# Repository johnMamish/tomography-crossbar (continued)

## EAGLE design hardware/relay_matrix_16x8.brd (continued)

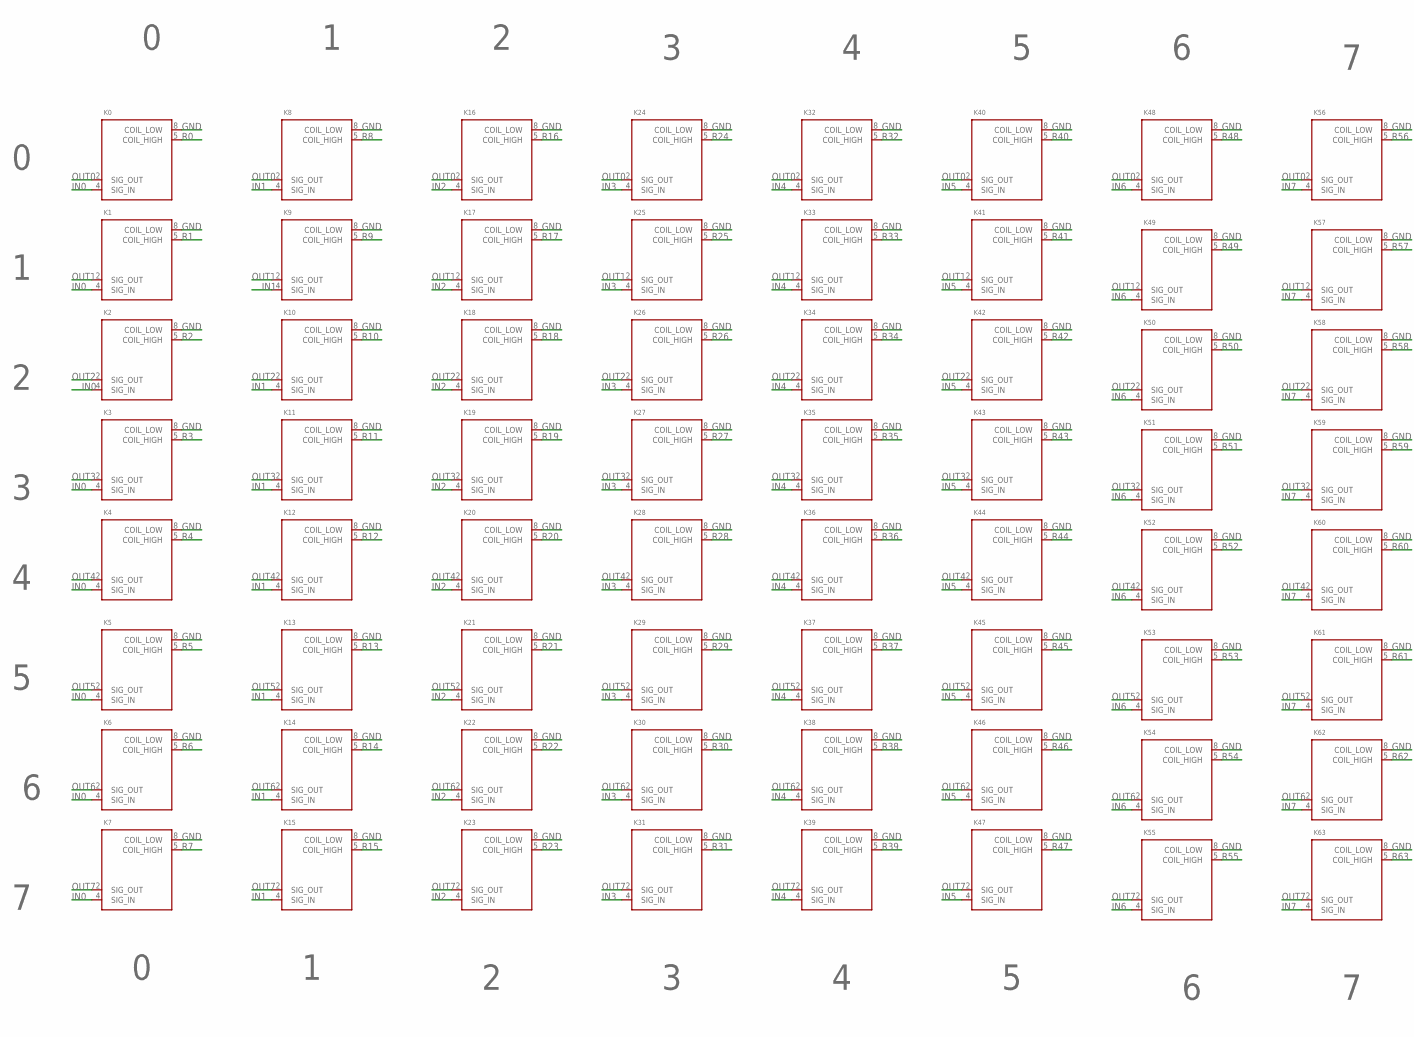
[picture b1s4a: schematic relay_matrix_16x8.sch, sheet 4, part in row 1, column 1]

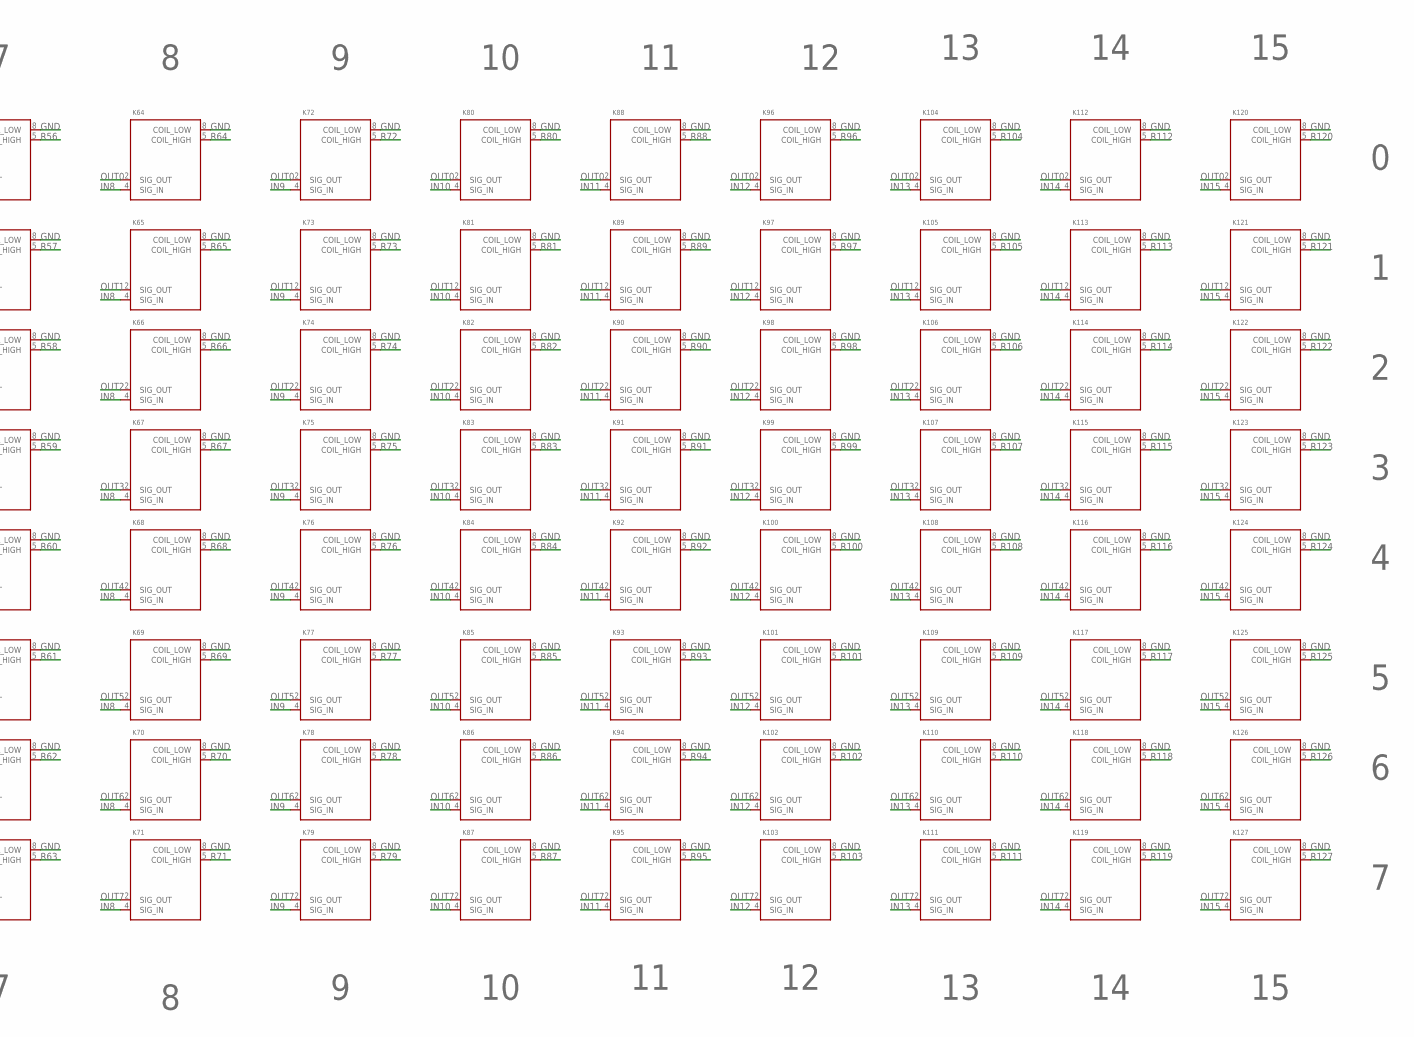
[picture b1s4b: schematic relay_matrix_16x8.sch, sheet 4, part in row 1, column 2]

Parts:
K0, K1, K2, K3, K4, K5, K6, K7, K8, K9, K10, K11, K12, K13, K14, K15, K16, K17, K18, K19, K20, K21, K22, K23, K24, K25, K26, K27, K28, K29, K30, K31, K32, K33, K34, K35, K36, K37, K38, K39, K40, K41, K42, K43, K44, K45, K46, K47, K48, K49, K50, K51, K52, K53, K54, K55, K56, K57, K58, K59, K60, K61, K62, K63, K64, K65, K66, K67, K68, K69, K70, K71, K72, K73, K74, K75, K76, K77, K78, K79, K80, K81, K82, K83, K84, K85, K86, K87, K88, K89, K90, K91, K92, K93, K94, K95, K96, K97, K98, K99, K100, K101, K102, K103, K104, K105, K106, K107, K108, K109, K110, K111, K112, K113, K114, K115, K116, K117, K118, K119, K120, K121, K122, K123, K124, K125, K126, K127: G6L-1F-DC4.5; MANUFACTURER_PART_NUMBER G6L-1F-DC4.5

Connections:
GND: K0.8 (COIL_LOW), K1.8 (COIL_LOW), K2.8 (COIL_LOW), K3.8 (COIL_LOW), K4.8 (COIL_LOW), K5.8 (COIL_LOW), K6.8 (COIL_LOW), K7.8 (COIL_LOW), K8.8 (COIL_LOW), K9.8 (COIL_LOW), K10.8 (COIL_LOW), K11.8 (COIL_LOW), K12.8 (COIL_LOW), K13.8 (COIL_LOW), K14.8 (COIL_LOW), K15.8 (COIL_LOW), K16.8 (COIL_LOW), K17.8 (COIL_LOW), K18.8 (COIL_LOW), K19.8 (COIL_LOW), K20.8 (COIL_LOW), K21.8 (COIL_LOW), K22.8 (COIL_LOW), K23.8 (COIL_LOW), K24.8 (COIL_LOW), K25.8 (COIL_LOW), K26.8 (COIL_LOW), K27.8 (COIL_LOW), K28.8 (COIL_LOW), K29.8 (COIL_LOW), K30.8 (COIL_LOW), K31.8 (COIL_LOW), K32.8 (COIL_LOW), K33.8 (COIL_LOW), K34.8 (COIL_LOW), K35.8 (COIL_LOW), K36.8 (COIL_LOW), K37.8 (COIL_LOW), K38.8 (COIL_LOW), K39.8 (COIL_LOW), K40.8 (COIL_LOW), K41.8 (COIL_LOW), K42.8 (COIL_LOW), K43.8 (COIL_LOW), K44.8 (COIL_LOW), K45.8 (COIL_LOW), K46.8 (COIL_LOW), K47.8 (COIL_LOW), K48.8 (COIL_LOW), K49.8 (COIL_LOW), K50.8 (COIL_LOW), K51.8 (COIL_LOW), K52.8 (COIL_LOW), K53.8 (COIL_LOW), K54.8 (COIL_LOW), K55.8 (COIL_LOW), K56.8 (COIL_LOW), K57.8 (COIL_LOW), K58.8 (COIL_LOW), K59.8 (COIL_LOW), K60.8 (COIL_LOW), K61.8 (COIL_LOW), K62.8 (COIL_LOW), K63.8 (COIL_LOW), K64.8 (COIL_LOW), K65.8 (COIL_LOW), K66.8 (COIL_LOW), K67.8 (COIL_LOW), K68.8 (COIL_LOW), K69.8 (COIL_LOW), K70.8 (COIL_LOW), K71.8 (COIL_LOW), K72.8 (COIL_LOW), K73.8 (COIL_LOW), K74.8 (COIL_LOW), K75.8 (COIL_LOW), K76.8 (COIL_LOW), K77.8 (COIL_LOW), K78.8 (COIL_LOW), K79.8 (COIL_LOW), K80.8 (COIL_LOW), K81.8 (COIL_LOW), K82.8 (COIL_LOW), K83.8 (COIL_LOW), K84.8 (COIL_LOW), K85.8 (COIL_LOW), K86.8 (COIL_LOW), K87.8 (COIL_LOW), K88.8 (COIL_LOW), K89.8 (COIL_LOW), K90.8 (COIL_LOW), K91.8 (COIL_LOW), K92.8 (COIL_LOW), K93.8 (COIL_LOW), K94.8 (COIL_LOW), K95.8 (COIL_LOW), K96.8 (COIL_LOW), K97.8 (COIL_LOW), K98.8 (COIL_LOW), K99.8 (COIL_LOW), K100.8 (COIL_LOW), K101.8 (COIL_LOW), K102.8 (COIL_LOW), K103.8 (COIL_LOW), K104.8 (COIL_LOW), K105.8 (COIL_LOW), K106.8 (COIL_LOW), K107.8 (COIL_LOW), K108.8 (COIL_LOW), K109.8 (COIL_LOW), K110.8 (COIL_LOW), K111.8 (COIL_LOW), K112.8 (COIL_LOW), K113.8 (COIL_LOW), K114.8 (COIL_LOW), K115.8 (COIL_LOW), K116.8 (COIL_LOW), K117.8 (COIL_LOW), K118.8 (COIL_LOW), K119.8 (COIL_LOW), K120.8 (COIL_LOW), K121.8 (COIL_LOW), K122.8 (COIL_LOW), K123.8 (COIL_LOW), K124.8 (COIL_LOW), K125.8 (COIL_LOW), K126.8 (COIL_LOW), K127.8 (COIL_LOW); also elsewhere on the board
IN0: K0.4 (SIG_IN), K1.4 (SIG_IN), K2.4 (SIG_IN), K3.4 (SIG_IN), K4.4 (SIG_IN), K5.4 (SIG_IN), K6.4 (SIG_IN), K7.4 (SIG_IN); also elsewhere on the board
IN1: K8.4 (SIG_IN), K9.4 (SIG_IN), K10.4 (SIG_IN), K11.4 (SIG_IN), K12.4 (SIG_IN), K13.4 (SIG_IN), K14.4 (SIG_IN), K15.4 (SIG_IN); also elsewhere on the board
IN2: K16.4 (SIG_IN), K17.4 (SIG_IN), K18.4 (SIG_IN), K19.4 (SIG_IN), K20.4 (SIG_IN), K21.4 (SIG_IN), K22.4 (SIG_IN), K23.4 (SIG_IN); also elsewhere on the board
IN3: K24.4 (SIG_IN), K25.4 (SIG_IN), K26.4 (SIG_IN), K27.4 (SIG_IN), K28.4 (SIG_IN), K29.4 (SIG_IN), K30.4 (SIG_IN), K31.4 (SIG_IN); also elsewhere on the board
IN4: K32.4 (SIG_IN), K33.4 (SIG_IN), K34.4 (SIG_IN), K35.4 (SIG_IN), K36.4 (SIG_IN), K37.4 (SIG_IN), K38.4 (SIG_IN), K39.4 (SIG_IN); also elsewhere on the board
IN5: K40.4 (SIG_IN), K41.4 (SIG_IN), K42.4 (SIG_IN), K43.4 (SIG_IN), K44.4 (SIG_IN), K45.4 (SIG_IN), K46.4 (SIG_IN), K47.4 (SIG_IN); also elsewhere on the board
IN6: K48.4 (SIG_IN), K49.4 (SIG_IN), K50.4 (SIG_IN), K51.4 (SIG_IN), K52.4 (SIG_IN), K53.4 (SIG_IN), K54.4 (SIG_IN), K55.4 (SIG_IN); also elsewhere on the board
IN7: K56.4 (SIG_IN), K57.4 (SIG_IN), K58.4 (SIG_IN), K59.4 (SIG_IN), K60.4 (SIG_IN), K61.4 (SIG_IN), K62.4 (SIG_IN), K63.4 (SIG_IN); also elsewhere on the board
IN8: K64.4 (SIG_IN), K65.4 (SIG_IN), K66.4 (SIG_IN), K67.4 (SIG_IN), K68.4 (SIG_IN), K69.4 (SIG_IN), K70.4 (SIG_IN), K71.4 (SIG_IN); also elsewhere on the board
IN9: K72.4 (SIG_IN), K73.4 (SIG_IN), K74.4 (SIG_IN), K75.4 (SIG_IN), K76.4 (SIG_IN), K77.4 (SIG_IN), K78.4 (SIG_IN), K79.4 (SIG_IN); also elsewhere on the board
IN10: K80.4 (SIG_IN), K81.4 (SIG_IN), K82.4 (SIG_IN), K83.4 (SIG_IN), K84.4 (SIG_IN), K85.4 (SIG_IN), K86.4 (SIG_IN), K87.4 (SIG_IN); also elsewhere on the board
IN11: K88.4 (SIG_IN), K89.4 (SIG_IN), K90.4 (SIG_IN), K91.4 (SIG_IN), K92.4 (SIG_IN), K93.4 (SIG_IN), K94.4 (SIG_IN), K95.4 (SIG_IN); also elsewhere on the board
IN12: K96.4 (SIG_IN), K97.4 (SIG_IN), K98.4 (SIG_IN), K99.4 (SIG_IN), K100.4 (SIG_IN), K101.4 (SIG_IN), K102.4 (SIG_IN), K103.4 (SIG_IN); also elsewhere on the board
IN13: K104.4 (SIG_IN), K105.4 (SIG_IN), K106.4 (SIG_IN), K107.4 (SIG_IN), K108.4 (SIG_IN), K109.4 (SIG_IN), K110.4 (SIG_IN), K111.4 (SIG_IN); also elsewhere on the board
IN14: K112.4 (SIG_IN), K113.4 (SIG_IN), K114.4 (SIG_IN), K115.4 (SIG_IN), K116.4 (SIG_IN), K117.4 (SIG_IN), K118.4 (SIG_IN), K119.4 (SIG_IN); also elsewhere on the board
IN15: K120.4 (SIG_IN), K121.4 (SIG_IN), K122.4 (SIG_IN), K123.4 (SIG_IN), K124.4 (SIG_IN), K125.4 (SIG_IN), K126.4 (SIG_IN), K127.4 (SIG_IN); also elsewhere on the board
OUT0: K0.2 (SIG_OUT), K8.2 (SIG_OUT), K16.2 (SIG_OUT), K24.2 (SIG_OUT), K32.2 (SIG_OUT), K40.2 (SIG_OUT), K48.2 (SIG_OUT), K56.2 (SIG_OUT), K64.2 (SIG_OUT), K72.2 (SIG_OUT), K80.2 (SIG_OUT), K88.2 (SIG_OUT), K96.2 (SIG_OUT), K104.2 (SIG_OUT), K112.2 (SIG_OUT), K120.2 (SIG_OUT); also elsewhere on the board
OUT1: K1.2 (SIG_OUT), K9.2 (SIG_OUT), K17.2 (SIG_OUT), K25.2 (SIG_OUT), K33.2 (SIG_OUT), K41.2 (SIG_OUT), K49.2 (SIG_OUT), K57.2 (SIG_OUT), K65.2 (SIG_OUT), K73.2 (SIG_OUT), K81.2 (SIG_OUT), K89.2 (SIG_OUT), K97.2 (SIG_OUT), K105.2 (SIG_OUT), K113.2 (SIG_OUT), K121.2 (SIG_OUT); also elsewhere on the board
OUT2: K2.2 (SIG_OUT), K10.2 (SIG_OUT), K18.2 (SIG_OUT), K26.2 (SIG_OUT), K34.2 (SIG_OUT), K42.2 (SIG_OUT), K50.2 (SIG_OUT), K58.2 (SIG_OUT), K66.2 (SIG_OUT), K74.2 (SIG_OUT), K82.2 (SIG_OUT), K90.2 (SIG_OUT), K98.2 (SIG_OUT), K106.2 (SIG_OUT), K114.2 (SIG_OUT), K122.2 (SIG_OUT); also elsewhere on the board
OUT3: K3.2 (SIG_OUT), K11.2 (SIG_OUT), K19.2 (SIG_OUT), K27.2 (SIG_OUT), K35.2 (SIG_OUT), K43.2 (SIG_OUT), K51.2 (SIG_OUT), K59.2 (SIG_OUT), K67.2 (SIG_OUT), K75.2 (SIG_OUT), K83.2 (SIG_OUT), K91.2 (SIG_OUT), K99.2 (SIG_OUT), K107.2 (SIG_OUT), K115.2 (SIG_OUT), K123.2 (SIG_OUT); also elsewhere on the board
OUT4: K4.2 (SIG_OUT), K12.2 (SIG_OUT), K20.2 (SIG_OUT), K28.2 (SIG_OUT), K36.2 (SIG_OUT), K44.2 (SIG_OUT), K52.2 (SIG_OUT), K60.2 (SIG_OUT), K68.2 (SIG_OUT), K76.2 (SIG_OUT), K84.2 (SIG_OUT), K92.2 (SIG_OUT), K100.2 (SIG_OUT), K108.2 (SIG_OUT), K116.2 (SIG_OUT), K124.2 (SIG_OUT); also elsewhere on the board
OUT5: K5.2 (SIG_OUT), K13.2 (SIG_OUT), K21.2 (SIG_OUT), K29.2 (SIG_OUT), K37.2 (SIG_OUT), K45.2 (SIG_OUT), K53.2 (SIG_OUT), K61.2 (SIG_OUT), K69.2 (SIG_OUT), K77.2 (SIG_OUT), K85.2 (SIG_OUT), K93.2 (SIG_OUT), K101.2 (SIG_OUT), K109.2 (SIG_OUT), K117.2 (SIG_OUT), K125.2 (SIG_OUT); also elsewhere on the board
OUT6: K6.2 (SIG_OUT), K14.2 (SIG_OUT), K22.2 (SIG_OUT), K30.2 (SIG_OUT), K38.2 (SIG_OUT), K46.2 (SIG_OUT), K54.2 (SIG_OUT), K62.2 (SIG_OUT), K70.2 (SIG_OUT), K78.2 (SIG_OUT), K86.2 (SIG_OUT), K94.2 (SIG_OUT), K102.2 (SIG_OUT), K110.2 (SIG_OUT), K118.2 (SIG_OUT), K126.2 (SIG_OUT); also elsewhere on the board
OUT7: K7.2 (SIG_OUT), K15.2 (SIG_OUT), K23.2 (SIG_OUT), K31.2 (SIG_OUT), K39.2 (SIG_OUT), K47.2 (SIG_OUT), K55.2 (SIG_OUT), K63.2 (SIG_OUT), K71.2 (SIG_OUT), K79.2 (SIG_OUT), K87.2 (SIG_OUT), K95.2 (SIG_OUT), K103.2 (SIG_OUT), K111.2 (SIG_OUT), K119.2 (SIG_OUT), K127.2 (SIG_OUT); also elsewhere on the board
R0: K0.5 (COIL_HIGH); also elsewhere on the board
R1: K1.5 (COIL_HIGH); also elsewhere on the board
R2: K2.5 (COIL_HIGH); also elsewhere on the board
R3: K3.5 (COIL_HIGH); also elsewhere on the board
R4: K4.5 (COIL_HIGH); also elsewhere on the board
R5: K5.5 (COIL_HIGH); also elsewhere on the board
R6: K6.5 (COIL_HIGH); also elsewhere on the board
R7: K7.5 (COIL_HIGH); also elsewhere on the board
R8: K8.5 (COIL_HIGH); also elsewhere on the board
R9: K9.5 (COIL_HIGH); also elsewhere on the board
R10: K10.5 (COIL_HIGH); also elsewhere on the board
R11: K11.5 (COIL_HIGH); also elsewhere on the board
R12: K12.5 (COIL_HIGH); also elsewhere on the board
R13: K13.5 (COIL_HIGH); also elsewhere on the board
R14: K14.5 (COIL_HIGH); also elsewhere on the board
R15: K15.5 (COIL_HIGH); also elsewhere on the board
R16: K16.5 (COIL_HIGH); also elsewhere on the board
R17: K17.5 (COIL_HIGH); also elsewhere on the board
R18: K18.5 (COIL_HIGH); also elsewhere on the board
R19: K19.5 (COIL_HIGH); also elsewhere on the board
R20: K20.5 (COIL_HIGH); also elsewhere on the board
R21: K21.5 (COIL_HIGH); also elsewhere on the board
R22: K22.5 (COIL_HIGH); also elsewhere on the board
R23: K23.5 (COIL_HIGH); also elsewhere on the board
R24: K24.5 (COIL_HIGH); also elsewhere on the board
R25: K25.5 (COIL_HIGH); also elsewhere on the board
R26: K26.5 (COIL_HIGH); also elsewhere on the board
R27: K27.5 (COIL_HIGH); also elsewhere on the board
R28: K28.5 (COIL_HIGH); also elsewhere on the board
R29: K29.5 (COIL_HIGH); also elsewhere on the board
R30: K30.5 (COIL_HIGH); also elsewhere on the board
R31: K31.5 (COIL_HIGH); also elsewhere on the board
R32: K32.5 (COIL_HIGH); also elsewhere on the board
R33: K33.5 (COIL_HIGH); also elsewhere on the board
R34: K34.5 (COIL_HIGH); also elsewhere on the board
R35: K35.5 (COIL_HIGH); also elsewhere on the board
R36: K36.5 (COIL_HIGH); also elsewhere on the board
R37: K37.5 (COIL_HIGH); also elsewhere on the board
R38: K38.5 (COIL_HIGH); also elsewhere on the board
R39: K39.5 (COIL_HIGH); also elsewhere on the board
R40: K40.5 (COIL_HIGH); also elsewhere on the board
R41: K41.5 (COIL_HIGH); also elsewhere on the board
R42: K42.5 (COIL_HIGH); also elsewhere on the board
R43: K43.5 (COIL_HIGH); also elsewhere on the board
R44: K44.5 (COIL_HIGH); also elsewhere on the board
R45: K45.5 (COIL_HIGH); also elsewhere on the board
R46: K46.5 (COIL_HIGH); also elsewhere on the board
R47: K47.5 (COIL_HIGH); also elsewhere on the board
R48: K48.5 (COIL_HIGH); also elsewhere on the board
R49: K49.5 (COIL_HIGH); also elsewhere on the board
R50: K50.5 (COIL_HIGH); also elsewhere on the board
R51: K51.5 (COIL_HIGH); also elsewhere on the board
R52: K52.5 (COIL_HIGH); also elsewhere on the board
R53: K53.5 (COIL_HIGH); also elsewhere on the board
R54: K54.5 (COIL_HIGH); also elsewhere on the board
R55: K55.5 (COIL_HIGH); also elsewhere on the board
R56: K56.5 (COIL_HIGH); also elsewhere on the board
R57: K57.5 (COIL_HIGH); also elsewhere on the board
R58: K58.5 (COIL_HIGH); also elsewhere on the board
R59: K59.5 (COIL_HIGH); also elsewhere on the board
R60: K60.5 (COIL_HIGH); also elsewhere on the board
R61: K61.5 (COIL_HIGH); also elsewhere on the board
R62: K62.5 (COIL_HIGH); also elsewhere on the board
R63: K63.5 (COIL_HIGH); also elsewhere on the board
R64: K64.5 (COIL_HIGH); also elsewhere on the board
R65: K65.5 (COIL_HIGH); also elsewhere on the board
R66: K66.5 (COIL_HIGH); also elsewhere on the board
R67: K67.5 (COIL_HIGH); also elsewhere on the board
R68: K68.5 (COIL_HIGH); also elsewhere on the board
R69: K69.5 (COIL_HIGH); also elsewhere on the board
R70: K70.5 (COIL_HIGH); also elsewhere on the board
R71: K71.5 (COIL_HIGH); also elsewhere on the board
R72: K72.5 (COIL_HIGH); also elsewhere on the board
R73: K73.5 (COIL_HIGH); also elsewhere on the board
R74: K74.5 (COIL_HIGH); also elsewhere on the board
R75: K75.5 (COIL_HIGH); also elsewhere on the board
R76: K76.5 (COIL_HIGH); also elsewhere on the board
R77: K77.5 (COIL_HIGH); also elsewhere on the board
R78: K78.5 (COIL_HIGH); also elsewhere on the board
R79: K79.5 (COIL_HIGH); also elsewhere on the board
R80: K80.5 (COIL_HIGH); also elsewhere on the board
R81: K81.5 (COIL_HIGH); also elsewhere on the board
R82: K82.5 (COIL_HIGH); also elsewhere on the board
R83: K83.5 (COIL_HIGH); also elsewhere on the board
R84: K84.5 (COIL_HIGH); also elsewhere on the board
R85: K85.5 (COIL_HIGH); also elsewhere on the board
R86: K86.5 (COIL_HIGH); also elsewhere on the board
R87: K87.5 (COIL_HIGH); also elsewhere on the board
R88: K88.5 (COIL_HIGH); also elsewhere on the board
R89: K89.5 (COIL_HIGH); also elsewhere on the board
R90: K90.5 (COIL_HIGH); also elsewhere on the board
R91: K91.5 (COIL_HIGH); also elsewhere on the board
R92: K92.5 (COIL_HIGH); also elsewhere on the board
R93: K93.5 (COIL_HIGH); also elsewhere on the board
R94: K94.5 (COIL_HIGH); also elsewhere on the board
R95: K95.5 (COIL_HIGH); also elsewhere on the board
R96: K96.5 (COIL_HIGH); also elsewhere on the board
R97: K97.5 (COIL_HIGH); also elsewhere on the board
R98: K98.5 (COIL_HIGH); also elsewhere on the board
R99: K99.5 (COIL_HIGH); also elsewhere on the board
R100: K100.5 (COIL_HIGH); also elsewhere on the board
R101: K101.5 (COIL_HIGH); also elsewhere on the board
R102: K102.5 (COIL_HIGH); also elsewhere on the board
R103: K103.5 (COIL_HIGH); also elsewhere on the board
R104: K104.5 (COIL_HIGH); also elsewhere on the board
R105: K105.5 (COIL_HIGH); also elsewhere on the board
R106: K106.5 (COIL_HIGH); also elsewhere on the board
R107: K107.5 (COIL_HIGH); also elsewhere on the board
R108: K108.5 (COIL_HIGH); also elsewhere on the board
R109: K109.5 (COIL_HIGH); also elsewhere on the board
R110: K110.5 (COIL_HIGH); also elsewhere on the board
R111: K111.5 (COIL_HIGH); also elsewhere on the board
R112: K112.5 (COIL_HIGH); also elsewhere on the board
R113: K113.5 (COIL_HIGH); also elsewhere on the board
R114: K114.5 (COIL_HIGH); also elsewhere on the board
R115: K115.5 (COIL_HIGH); also elsewhere on the board
R116: K116.5 (COIL_HIGH); also elsewhere on the board
R117: K117.5 (COIL_HIGH); also elsewhere on the board
R118: K118.5 (COIL_HIGH); also elsewhere on the board
R119: K119.5 (COIL_HIGH); also elsewhere on the board
R120: K120.5 (COIL_HIGH); also elsewhere on the board
R121: K121.5 (COIL_HIGH); also elsewhere on the board
R122: K122.5 (COIL_HIGH); also elsewhere on the board
R123: K123.5 (COIL_HIGH); also elsewhere on the board
R124: K124.5 (COIL_HIGH); also elsewhere on the board
R125: K125.5 (COIL_HIGH); also elsewhere on the board
R126: K126.5 (COIL_HIGH); also elsewhere on the board
R127: K127.5 (COIL_HIGH); also elsewhere on the board

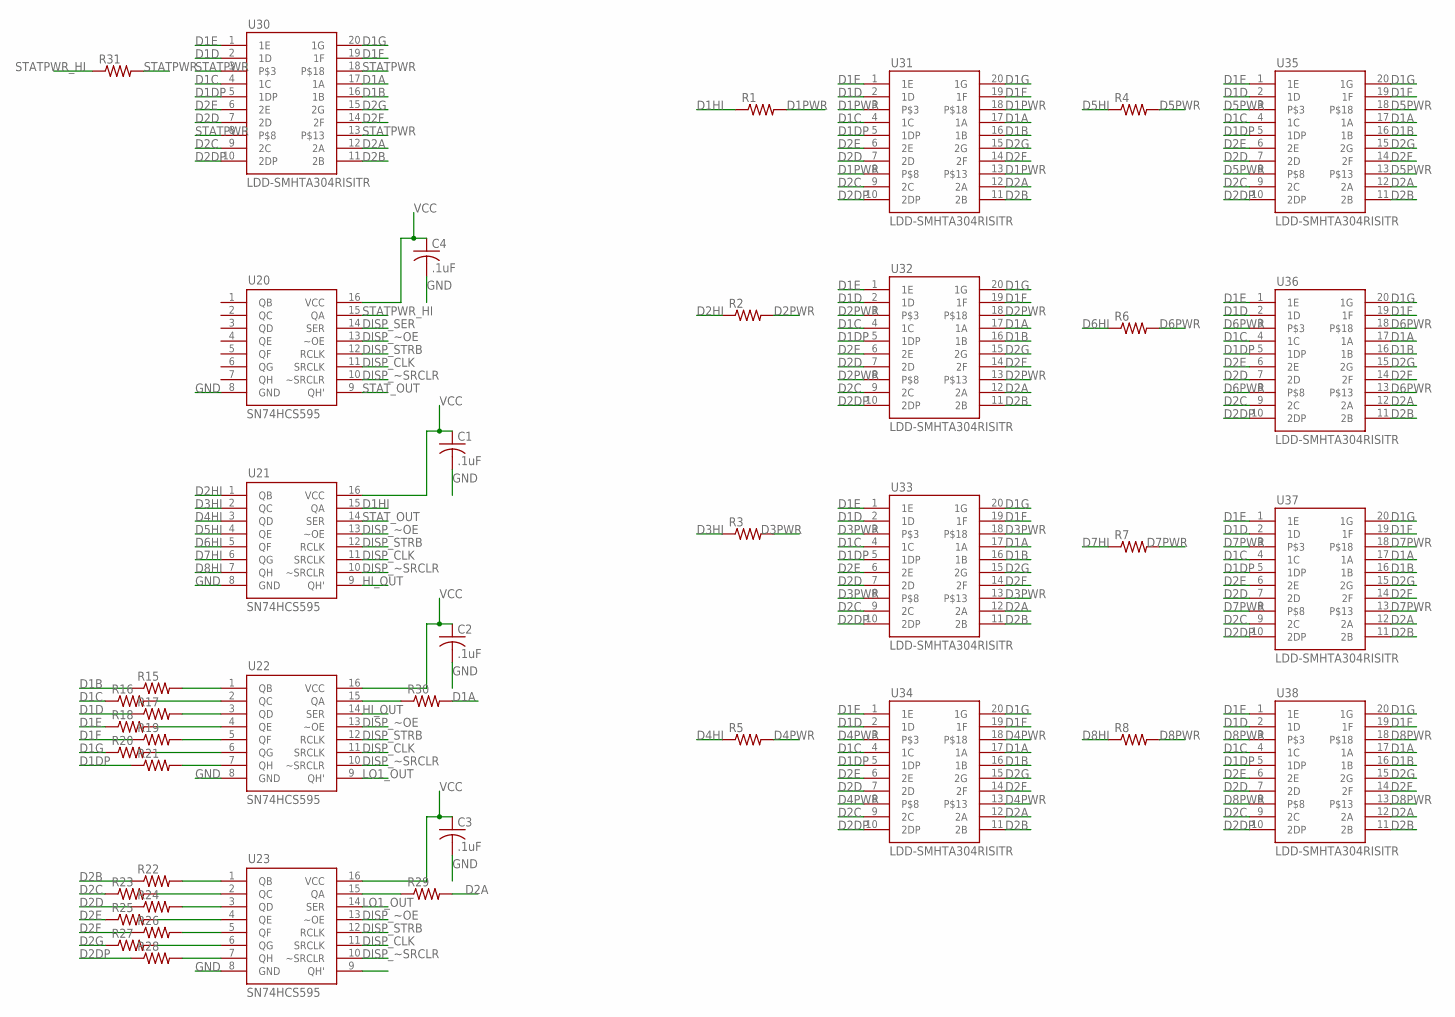
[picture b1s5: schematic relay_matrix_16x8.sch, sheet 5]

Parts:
C1, C2, C3, C4: .1uF; C0402; MANUFACTURER_PART_NUMBER CL05B104KO5NNNC
R1, R2, R3, R4, R5, R6, R7, R8, R15, R16, R17, R18, R19, R20, R21, R22, R23, R24, R25, R26, R27, R28, R29, R30, R31: R-US_R0402; R0402
U20, U21, U22, U23: SN74HCS595; SOP65P640X120-16N; MANUFACTURER_PART_NUMBER SN74HCS595PWR
U30, U31, U32, U33, U34, U35, U36, U37, U38: LDD-SMHTA304RISITR; LDD-SMHTA304RISITR-20DFN; MANUFACTURER_PART_NUMBER LDD-SMHTA304RISITR

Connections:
D1A: R30.2, U30.17 (1A), U31.17 (1A), U32.17 (1A), U33.17 (1A), U34.17 (1A), U35.17 (1A), U36.17 (1A), U37.17 (1A), U38.17 (1A)
D1B: R15.1, U30.16 (1B), U31.16 (1B), U32.16 (1B), U33.16 (1B), U34.16 (1B), U35.16 (1B), U36.16 (1B), U37.16 (1B), U38.16 (1B)
D1C: R16.1, U30.4 (1C), U31.4 (1C), U32.4 (1C), U33.4 (1C), U34.4 (1C), U35.4 (1C), U36.4 (1C), U37.4 (1C), U38.4 (1C)
D1D: R17.1, U30.2 (1D), U31.2 (1D), U32.2 (1D), U33.2 (1D), U34.2 (1D), U35.2 (1D), U36.2 (1D), U37.2 (1D), U38.2 (1D)
D1DP: R21.1, U30.5 (1DP), U31.5 (1DP), U32.5 (1DP), U33.5 (1DP), U34.5 (1DP), U35.5 (1DP), U36.5 (1DP), U37.5 (1DP), U38.5 (1DP)
D1E: R18.1, U30.1 (1E), U31.1 (1E), U32.1 (1E), U33.1 (1E), U34.1 (1E), U35.1 (1E), U36.1 (1E), U37.1 (1E), U38.1 (1E)
D1F: R19.1, U30.19 (1F), U31.19 (1F), U32.19 (1F), U33.19 (1F), U34.19 (1F), U35.19 (1F), U36.19 (1F), U37.19 (1F), U38.19 (1F)
D1G: R20.1, U30.20 (1G), U31.20 (1G), U32.20 (1G), U33.20 (1G), U34.20 (1G), U35.20 (1G), U36.20 (1G), U37.20 (1G), U38.20 (1G)
D1HI: R1.1, U21.15 (QA)
D1PWR: R1.2, U31.3, U31.8, U31.13, U31.18
D2A: R29.2, U30.12 (2A), U31.12 (2A), U32.12 (2A), U33.12 (2A), U34.12 (2A), U35.12 (2A), U36.12 (2A), U37.12 (2A), U38.12 (2A)
D2B: R22.1, U30.11 (2B), U31.11 (2B), U32.11 (2B), U33.11 (2B), U34.11 (2B), U35.11 (2B), U36.11 (2B), U37.11 (2B), U38.11 (2B)
D2C: R23.1, U30.9 (2C), U31.9 (2C), U32.9 (2C), U33.9 (2C), U34.9 (2C), U35.9 (2C), U36.9 (2C), U37.9 (2C), U38.9 (2C)
D2D: R24.1, U30.7 (2D), U31.7 (2D), U32.7 (2D), U33.7 (2D), U34.7 (2D), U35.7 (2D), U36.7 (2D), U37.7 (2D), U38.7 (2D)
D2DP: R28.1, U30.10 (2DP), U31.10 (2DP), U32.10 (2DP), U33.10 (2DP), U34.10 (2DP), U35.10 (2DP), U36.10 (2DP), U37.10 (2DP), U38.10 (2DP)
D2E: R25.1, U30.6 (2E), U31.6 (2E), U32.6 (2E), U33.6 (2E), U34.6 (2E), U35.6 (2E), U36.6 (2E), U37.6 (2E), U38.6 (2E)
D2F: R26.1, U30.14 (2F), U31.14 (2F), U32.14 (2F), U33.14 (2F), U34.14 (2F), U35.14 (2F), U36.14 (2F), U37.14 (2F), U38.14 (2F)
D2G: R27.1, U30.15 (2G), U31.15 (2G), U32.15 (2G), U33.15 (2G), U34.15 (2G), U35.15 (2G), U36.15 (2G), U37.15 (2G), U38.15 (2G)
D2HI: R2.1, U21.1 (QB)
D2PWR: R2.2, U32.3, U32.8, U32.13, U32.18
D3HI: R3.1, U21.2 (QC)
D3PWR: R3.2, U33.3, U33.8, U33.13, U33.18
D4HI: R5.1, U21.3 (QD)
D4PWR: R5.2, U34.3, U34.8, U34.13, U34.18
D5HI: R4.1, U21.4 (QE)
D5PWR: R4.2, U35.3, U35.8, U35.13, U35.18
D6HI: R6.1, U21.5 (QF)
D6PWR: R6.2, U36.3, U36.8, U36.13, U36.18
D7HI: R7.1, U21.6 (QG)
D7PWR: R7.2, U37.3, U37.8, U37.13, U37.18
D8HI: R8.1, U21.7 (QH)
D8PWR: R8.2, U38.3, U38.8, U38.13, U38.18
DISP_CLK: U20.11 (SRCLK), U21.11 (SRCLK), U22.11 (SRCLK), U23.11 (SRCLK); also elsewhere on the board
DISP_SER: U20.14 (SER); also elsewhere on the board
DISP_STRB: U20.12 (RCLK), U21.12 (RCLK), U22.12 (RCLK), U23.12 (RCLK); also elsewhere on the board
DISP_~OE: U20.13 (~OE), U21.13 (~OE), U22.13 (~OE), U23.13 (~OE); also elsewhere on the board
DISP_~SRCLR: U20.10 (~SRCLR), U21.10 (~SRCLR), U22.10 (~SRCLR), U23.10 (~SRCLR); also elsewhere on the board
GND: C1.2, C2.2, C3.2, C4.2, U20.8 (GND), U21.8 (GND), U22.8 (GND), U23.8 (GND); also elsewhere on the board
HI_OUT: U21.9 (QH'), U22.14 (SER)
LO1_OUT: U22.9 (QH'), U23.14 (SER)
unnamed: R30.1, U22.15 (QA)
unnamed: R22.2, U23.1 (QB)
unnamed: R15.2, U22.1 (QB)
unnamed: R23.2, U23.2 (QC)
unnamed: R24.2, U23.3 (QD)
unnamed: R16.2, U22.2 (QC)
unnamed: R17.2, U22.3 (QD)
unnamed: R18.2, U22.4 (QE)
unnamed: R19.2, U22.5 (QF)
unnamed: R20.2, U22.6 (QG)
unnamed: R21.2, U22.7 (QH)
unnamed: R25.2, U23.4 (QE)
unnamed: R26.2, U23.5 (QF)
unnamed: R27.2, U23.6 (QG)
unnamed: R28.2, U23.7 (QH)
unnamed: R29.1, U23.15 (QA)
STATPWR: R31.2, U30.3, U30.8, U30.13, U30.18
STATPWR_HI: R31.1, U20.15 (QA)
STAT_OUT: U20.9 (QH'), U21.14 (SER)
VCC: C1.1, C2.1, C3.1, C4.1, U20.16 (VCC), U21.16 (VCC), U22.16 (VCC), U23.16 (VCC); also elsewhere on the board

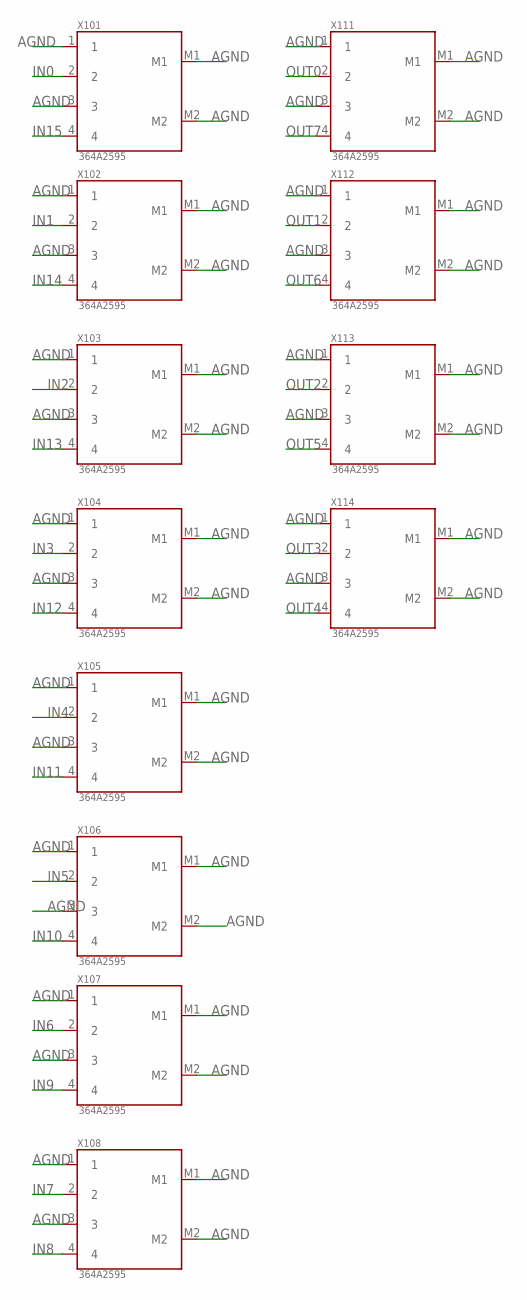
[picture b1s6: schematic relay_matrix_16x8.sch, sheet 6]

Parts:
X101, X102, X103, X104, X105, X106, X107, X108, X111, X112, X113, X114: 364A2595; MANUFACTURER_PART_NUMBER 364A2595

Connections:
AGND: X101.1, X101.3, X101.M1, X101.M2, X102.1, X102.3, X102.M1, X102.M2, X103.1, X103.3, X103.M1, X103.M2, X104.1, X104.3, X104.M1, X104.M2, X105.1, X105.3, X105.M1, X105.M2, X106.1, X106.3, X106.M1, X106.M2, X107.1, X107.3, X107.M1, X107.M2, X108.1, X108.3, X108.M1, X108.M2, X111.1, X111.3, X111.M1, X111.M2, X112.1, X112.3, X112.M1, X112.M2, X113.1, X113.3, X113.M1, X113.M2, X114.1, X114.3, X114.M1, X114.M2; also elsewhere on the board
IN0: X101.2; also elsewhere on the board
IN1: X102.2; also elsewhere on the board
IN2: X103.2; also elsewhere on the board
IN3: X104.2; also elsewhere on the board
IN4: X105.2; also elsewhere on the board
IN5: X106.2; also elsewhere on the board
IN6: X107.2; also elsewhere on the board
IN7: X108.2; also elsewhere on the board
IN8: X108.4; also elsewhere on the board
IN9: X107.4; also elsewhere on the board
IN10: X106.4; also elsewhere on the board
IN11: X105.4; also elsewhere on the board
IN12: X104.4; also elsewhere on the board
IN13: X103.4; also elsewhere on the board
IN14: X102.4; also elsewhere on the board
IN15: X101.4; also elsewhere on the board
OUT0: X111.2; also elsewhere on the board
OUT1: X112.2; also elsewhere on the board
OUT2: X113.2; also elsewhere on the board
OUT3: X114.2; also elsewhere on the board
OUT4: X114.4; also elsewhere on the board
OUT5: X113.4; also elsewhere on the board
OUT6: X112.4; also elsewhere on the board
OUT7: X111.4; also elsewhere on the board

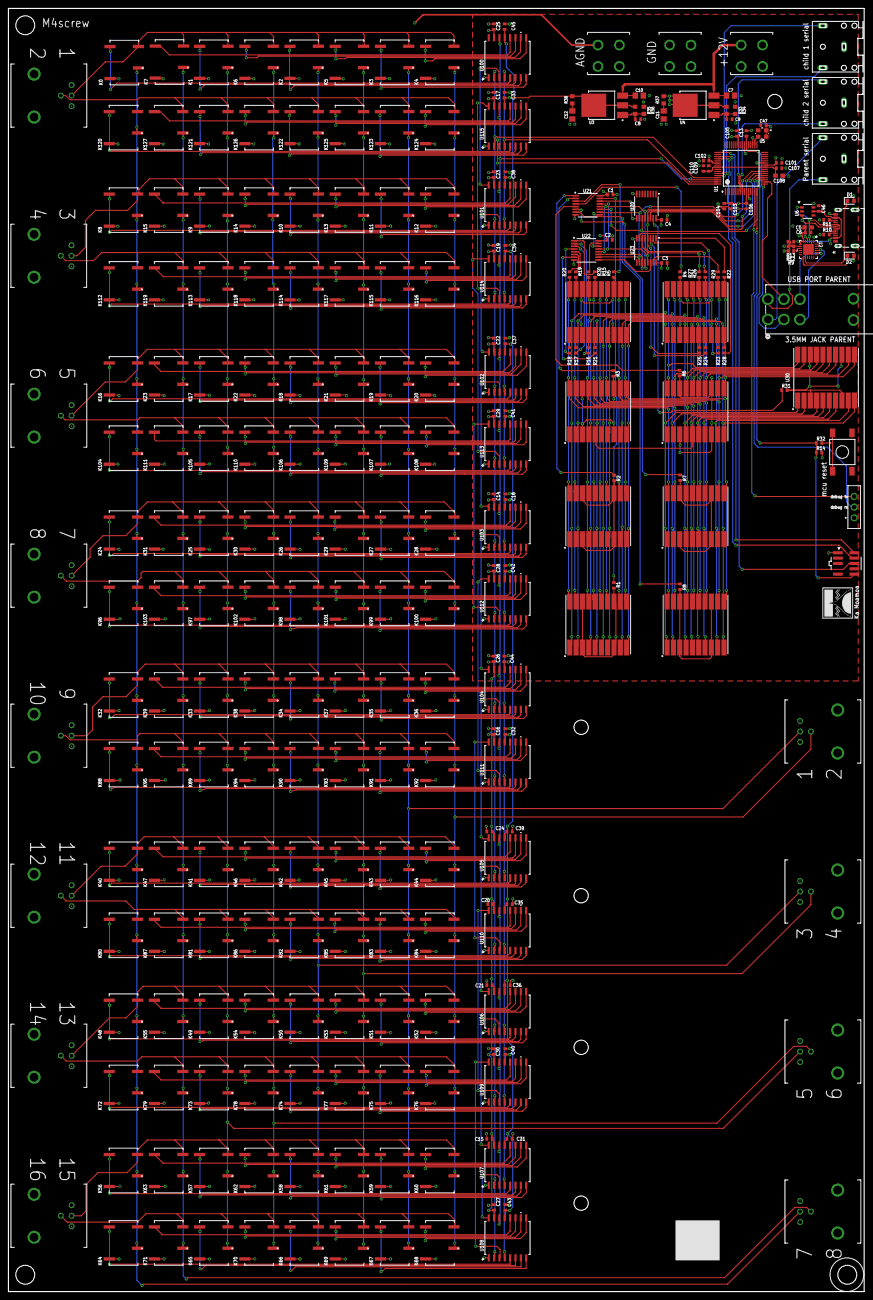
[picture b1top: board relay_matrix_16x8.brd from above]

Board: 4 copper layers, 203.2 x 304.7 mm, 283 parts (0 on the bottom side), 266 nets.

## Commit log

2022-02-25 initial commit with Connor's original design
2022-02-28 replace LDOs with more common part
2022-02-28 respace connectors; add mounting holes; add labels
2022-03-01 version sent to pcbway
2022-03-01 finish filling out part ordering info
2022-04-06 add more part names
2022-04-06 add header file from TI for MCU
2022-04-06 add bare basic files
2022-04-06 bringup relay drivers and LED drivers
2022-04-07 Squashed 'firmware/saeclib/' content from commit dfa403a
    git-subtree-dir: firmware/saeclib
    git-subtree-split: dfa403aeaa6d197b81bfb1e4836d50b807dcd877
2022-04-22 firmware wip
